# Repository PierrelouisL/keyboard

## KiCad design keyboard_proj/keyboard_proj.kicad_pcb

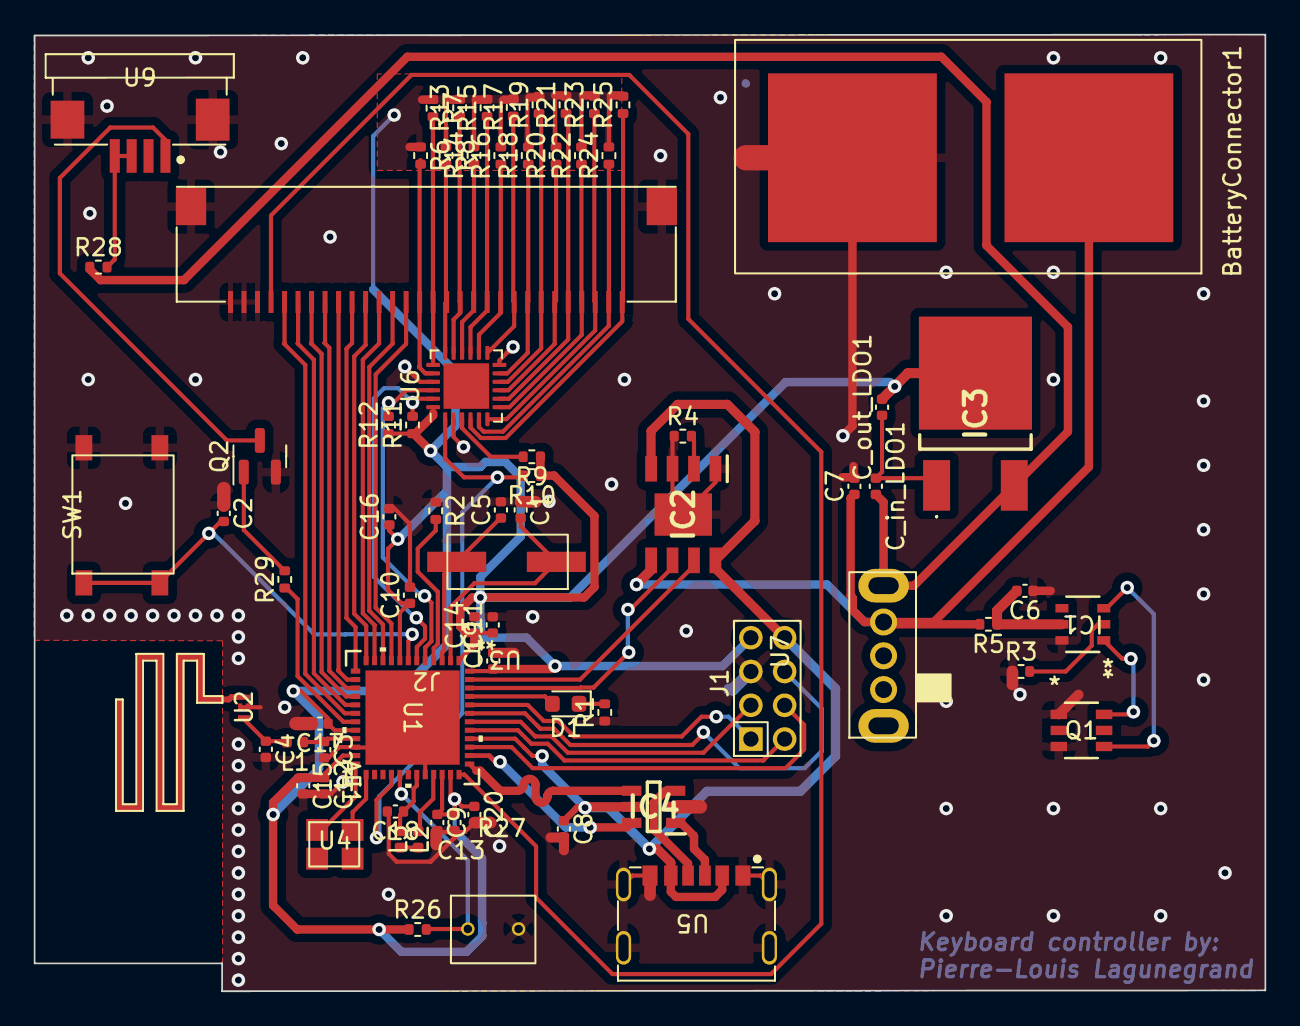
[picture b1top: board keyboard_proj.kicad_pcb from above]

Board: 2 copper layers, 72.9 x 56.6 mm, 74 parts (0 on the bottom side), 72 nets.

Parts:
AE1: Antenna; BLE_PCB_ant
BatteryConnector1: Conn_01x02; Bat_conn
C1, C5: 10pF; C_0402_1005Metric
C2: 0.1uF; C_0402_1005Metric
C3: 0.8pF; C_0402_1005Metric
C4: 0.3pF; C_0402_1005Metric
C6: 100 uF; C_0402_1005Metric
C7: 10 uF; C_0402_1005Metric
C8, C12, C13, C14, C17, C19, C20: 100nF; C_0402_1005Metric
C9, C11, C18: 4.7uF; C_0402_1005Metric
C10: 1uF; C_0402_1005Metric
C15: 100pF; C_0402_1005Metric
C16: 10nF; C_0402_1005Metric
C_in_LDO1: 100nF; C_0402_1005Metric
C_out_LDO1: 10uF; C_0402_1005Metric
D1: LED; LED_0603_1608Metric
IC1: DW01A-G; SOT-23-6L_TCP-L
IC2: TP4056-42-ESOP8; SOIC127P600X175-9N
IC3: LD1117DT12CTR
IC4: USBLC6-4SC6; SOT95P280X145-6N
J1: Conn_02x04_Odd_Even; debug_conn
J2: Conn_01x32; conn_keyboard
L1: 2.7nH; L_0402_1005Metric
L2, L3: 10nH; L_0402_1005Metric
Q1: FS8205A; SOT-23-6L_TCP
Q2: 2N7002; SOT-23
R1, R5: 100; R_0402_1005Metric
R2, R3: 1k; R_0402_1005Metric
R4: 1.2k; R_0402_1005Metric
R6, R7, R8, R9, R10, R11, R12, R13, R14, R15, R16, R17, R18, R19, R20, R21, R22, R23, R24, R25: 10k; R_0402_1005Metric
R26: 7.5k; R_0402_1005Metric
R27: R_Photo; R_photo
R28: 500; R_0402_1005Metric
R29: 300; R_0402_1005Metric
SW1: SW_Push; switch
U1: STM32WB55CGU6; UFQFPN48-7x7mm
U2: DLF162500LT-5028A1; DLF-4_1P6X0P8
U3: DP2032K76812001; Quartz-HC-49S-SMD-Mini
U4: SX3B32.000F1210F30; Quartz-SMD3225-4P
U5: 918-418K2023S40026; USB_conn
U6: XL9555QF24; QFN-24-1EP_4x4mm_P0.5mm_EP2.7x2.7mm
U7: SK12D07VG5; select_switch
U9: 1.0K-ES-4PWB

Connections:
/BacklightControl: R29.1, U1.19 (PB2)
/I2C1_SCL: R12.2, U1.5 (PB8), U6.22 (SCL)
/I2C1_SDA: R11.2, U1.6 (PB9), U6.23 (SDA)
/JTDI: J1.3, U1.42 (PA15)
/JTDO: J1.6, U1.43 (PB3)
/LightSensor: R26.2, R27.1, U1.29 (PB1)
/NJTRST: J1.1, U1.44 (PB4)
/OSC32_IN: C1.2, U1.2 (PC14-OSC32_IN), U3.1
/OSC32_OUT: C5.1, U1.3 (PC15-OSC32_OUT), U3.2
/Power/3.3V: C9.1, C10.1, C11.1, C12.1, C13.1, C14.1, C15.1, C16.1, C17.1, C19.1, C20.1, C_out_LDO1.2, IC3.2 (VOUT), J1.7, R6.1, R7.1, R8.1, R9.1, R10.1, R11.1, R12.1, R13.2, R14.2, R15.2, R16.2, R17.2, R18.2, R19.2, R20.2, R21.2, R22.2, R23.2, R24.2, R25.2, R26.1, U1.1 (VBAT), U1.8 (VDDA), U1.20 (VDD), U1.23 (VDDRF), U1.34 (VDDSMPS), U1.35 (VDD), U1.48 (VDD), U6.24 (VCC)
/SWCLK: J1.2, U1.41 (PA14)
/SWIO: J1.4, U1.39 (PA13)
/USB_N: IC4.4 (I/O2_2), U1.37 (PA11)
/USB_P: IC4.6 (I/O1_2), U1.38 (PA12)
/VBUS: C8.1, IC2.4 (VCC), IC2.8 (CE), IC4.5 (VBUS), J1.8, U1.40 (VDDUSB), U5.2 (VBUS), U5.5 (VBUS)
/battery_mgmnt/Vbat+: BatteryConnector1.1, C7.1, IC2.5 (BAT), R5.2, U7.3 (base)
/battery_mgmnt/sel_bat_out: C_in_LDO1.2, IC3.3 (VIN), R28.1, U7.4 (state2)
/chrg: IC2.7 (~CHRG), U1.47 (PB7)
/stby: IC2.6 (~STDBY), U1.46 (PB6)
//INT: R10.2, U1.28 (PB0), U6.1 (/INT)
GND: BatteryConnector1.2, C1.1, C2.1, C3.2, C4.2, C5.2, C6.1, C7.2, C8.2, C9.2, C10.2, C11.2, C12.2, C13.2, C14.2, C15.2, C16.2, C17.2, C18.2, C19.2, C20.2, IC1.6 (GND), IC2.1 (TEMP), IC2.3 (GND), IC2.9 (EP), IC4.2 (GND), J1.5, J2.28, J2.29, J2.30, J2.31, J2.32, Q1.1, Q1.3, Q2.2 (S), R1.1, R2.1, R3.1, R4.1, R27.2, SW1.1, U1.22 (RF0), U1.32 (VSSSMPS), U1.49 (EPAD), U2.2 (GND), U2.4 (GND), U5.1 (GND), U5.6 (GND), U5.7 (SHELL), U5.8 (SHELL), U5.9 (SHELL), U5.10 (SHELL), U6.2 (A1), U6.12 (GND), U6.21 (A0), U9.5 (SHIELD), U9.6 (SHIELD)
unnamed: AE1.1 (A), U2.3 (OUT)
unnamed: D1.2 (A), U1.45 (PB5)
unnamed: D1.1 (K), R1.2
unnamed: IC1.2 (CS), R3.2
unnamed: IC1.3 (OC), Q1.4
unnamed: IC1.1 (OD), Q1.6
unnamed: C6.2, IC1.5 (VCC), R5.1
unnamed: IC2.2 (PROG), R4.2
unnamed: C_in_LDO1.1, C_out_LDO1.1, IC3.1 (ADJ/GND)
unnamed: IC4.1 (I/O1_1), U5.3 (CC1)
unnamed: IC4.3 (I/O2_1), U5.4 (CC2)
unnamed: J2.1, R25.1, U6.4 (P00)
unnamed: J2.2, R24.1, U6.5 (P01)
unnamed: J2.3, R23.1, U6.6 (P02)
unnamed: J2.4, R22.1, U6.7 (P03)
unnamed: J2.5, R21.1, U6.8 (P04)
unnamed: J2.6, R20.1, U6.9 (P05)
unnamed: J2.7, R19.1, U6.10 (P06)
unnamed: J2.8, R18.1, U6.11 (P07)
unnamed: J2.9, R17.1, U6.13 (P10)
unnamed: J2.10, R16.1, U6.14 (P11)
unnamed: J2.11, R15.1, U6.15 (P12)
unnamed: J2.12, R14.1, U6.16 (P13)
unnamed: J2.13, R13.1, U6.17 (P14)
unnamed: J2.14, R8.2, U6.18 (P15)
unnamed: J2.15, R7.2, U6.19 (P16)
unnamed: J2.16, R6.2, U6.20 (P17)
unnamed: L2.2, L3.1
unnamed: Q2.3 (D), U9.1 (GND)
unnamed: Q2.1 (G), R29.2
unnamed: R28.2, U9.3 (VCC), U9.4 (VCC)
unnamed: C2.2, SW1.2, U1.7 (NRST)
unnamed: U1.25 (OSC_IN), U4.2
unnamed: U1.24 (OSC_OUT), U4.1
unnamed: R2.2, U1.4 (PH3-BOOT0)
unnamed: C3.1, L1.1, U1.21 (RF1)
unnamed: C18.1, L2.1, U1.31 (VFBSMPS)
unnamed: L3.2, U1.33 (VLXSMPS)
unnamed: C4.1, L1.2, U2.1 (IN)
unnamed: R9.2, U6.3 (A2)
PA0: J2.17, U1.9 (PA0)
PA1: J2.18, U1.10 (PA1)
PA2: J2.19, U1.11 (PA2)
PA3: J2.20, U1.12 (PA3)
PA4: J2.21, U1.13 (PA4)
PA5: J2.22, U1.14 (PA5)
PA6: J2.23, U1.15 (PA6)
PA7: J2.24, U1.16 (PA7)
PA8: J2.25, U1.17 (PA8)
PA9: J2.26, U1.18 (PA9)
PA10: J2.27, U1.36 (PA10)

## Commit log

2024-04-15 Tous les schematics vérifiés 1x
2024-04-16 Ajout backlight et light sensor (in progress)
2024-04-16 Ajout light sensor et controle avec mosfet pour backlight
2024-04-16 Ajout des empreintes, il en manque encore
2024-04-18 Empreintes finies, besoin de reverifier, disposition des composants sur la carte
2024-04-29 passage kicad 7, routing bien avancé
2024-05-03 Routing bientot fini check schematic et tout mettre sur la meme face
2024-05-03 Power dlvry changée, ok mtn, routing updated
2024-05-05 PCB bien avancé, presque fini mais je dois selectionner des pieces de jlcpcb pour baisser les couts
